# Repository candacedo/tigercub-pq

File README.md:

# TigerCub PocketQube Platform
TigerCub, an accessible, mission-agnostic PocketQube platform.

TigerCub is a satellite bus in the PocketQube form factor, designed to be accessible to students and amateur nanosatellite developers. It uses primarily commercial-off-the-shelf (COTS) components and relatively simple custom-designed PCBs, lowering barriers of entry for developers who are venturing into the PocketQube world. 

I developed TigerCub for my undergraduate senior independent work. The vast majority of design work is complete and some subsystems have been tested in laboratory environments, but the satellite bus has yet to undergo full functional testing and testing in flight-like environments. Please use at your own risk.     

## Technical Overview
TigerCub includes the following subsystems:
* on-board computer and attitude determination system,
* electrical power system,
* radio communication system, and 
* chassis.

The on-board computer/attitude determination system features an Arduino-programmable Teensy 4.0 as well as a COTS IMU and COTS MicroSD storage from SparkFun. The communication system uses the RockBLOCK 9603, a compact and lightweight communications module that transmits and receives via the Iridium network. The electrical power system is composed of a power management and distribution module designed by BHDynamics, custom-designed solar panels, and a Lithium-ion battery. These subsystems are all integrated into a sheet-metal chassis, with additional space for a payload. 

All CAD was created in PTC Creo Parametric (Version 9.0.0.0), which is free for students. All schematics and PCB designs were created in KiCAD, a free EDA software. 

## Documentation
For additional technical and operational details, including design decisions, bill of materials, power and thermal analyses, and sample code, see the "TigerCub_Report" PDF file in the repository. Please reach out to cdo32 \[at\] gatech \[dot\] edu or mgalvin \[at\] princeton \[dot\] edu for further questions. 

## Future Work & Things to Fix
A few features that should to be fixed/added (not an exhaustive list):
* Kill switches should serve as a break point between the battery and the on-board computer instead of just being connected to the on-board computer. This will involve some redesign of the backplate and wire routing. 
* Flight software needs to be developed for the EPS module and expanded upon for the flight computer. (See technical report for additional details.)
* The RockBLOCK radio system has two electrolyic supercapacitors that are a potential outgassing risk. These should be swapped out for space-qualified capacitors.
* The thermal analysis (see technical report) suggests that the spacecraft may operate outside the temperature limits of the battery. The battery should be insulated to protect it from temperature extremes. See technical report for a few suggestions.

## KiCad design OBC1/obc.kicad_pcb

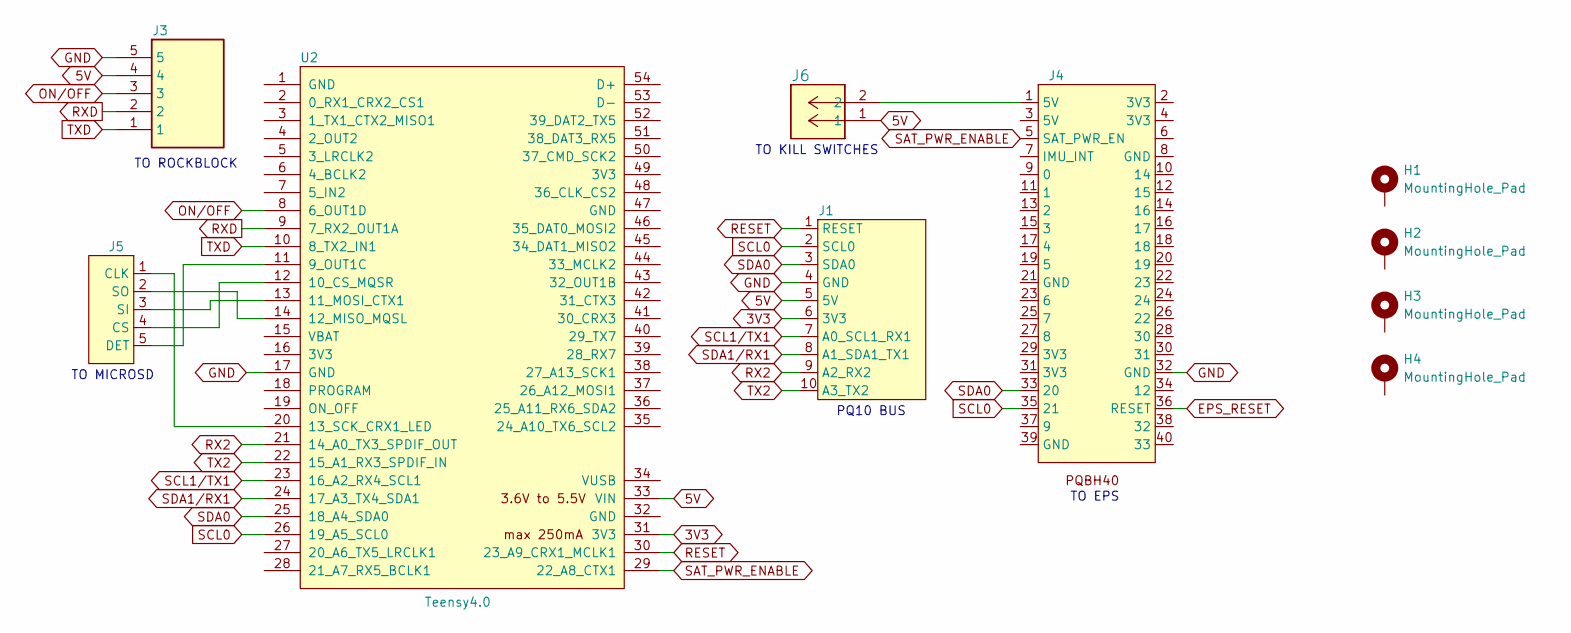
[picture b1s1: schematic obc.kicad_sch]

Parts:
H1, H2, H3, H4: MountingHole_Pad; MountingHole_2.5mm_Pad
J1: PinSocket_1x10_P2.00mm_Vertical
J2: (no value)
J3: 53048-0510; 530480510; Mouser Part Number 538-53048-0510
J4: PinSocket_2x20_P1.27mm_Vertical
J5: PinSocket_1x05_P2.00mm_Vertical
J6: 530480210; Molex_Picoblade_2x1_horz
U2: Teensy4.0; Teensy40

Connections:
3V3: J1.6 (3V3), U2.31 (3V3)
5V: J1.5 (5V), J3.4, J6.1, U2.33 (VIN)
EPS_RESET: J4.36 (RESET)
GND: J1.4 (GND), J3.5, J4.32 (GND), U2.17 (GND)
unnamed: J4.1 (5V), J6.2
unnamed: J5.1 (CLK), U2.20 (13_SCK_CRX1_LED)
unnamed: J5.4 (CS), U2.12 (10_CS_MQSR)
unnamed: J5.5 (DET), U2.11 (9_OUT1C)
unnamed: J5.3 (SI), U2.13 (11_MOSI_CTX1)
unnamed: J5.2 (SO), U2.14 (12_MISO_MQSL)
ON/OFF: J3.3, U2.8 (6_OUT1D)
RESET: J1.1 (RESET), U2.30 (23_A9_CRX1_MCLK1)
RX2: J1.9 (A2_RX2), U2.21 (14_A0_TX3_SPDIF_OUT)
RXD: J3.2, U2.9 (7_RX2_OUT1A)
SAT_PWR_ENABLE: J4.5 (SAT_PWR_EN), U2.29 (22_A8_CTX1)
SCL0: J1.2 (SCL0), J4.35 (21), U2.26 (19_A5_SCL0)
SCL1/TX1: J1.7 (A0_SCL1_RX1), U2.23 (16_A2_RX4_SCL1)
SDA0: J1.3 (SDA1), J4.33 (20), U2.25 (18_A4_SDA0)
SDA1/RX1: J1.8 (A1_SDA1_TX1), U2.24 (17_A3_TX4_SDA1)
TX2: J1.10 (A3_TX2), U2.22 (15_A1_RX3_SPDIF_IN)
TXD: J3.1, U2.10 (8_TX2_IN1)

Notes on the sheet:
TO KILL SWITCHES
PQ10 BUS
TO ROCKBLOCK
TO EPS
TO MICROSD

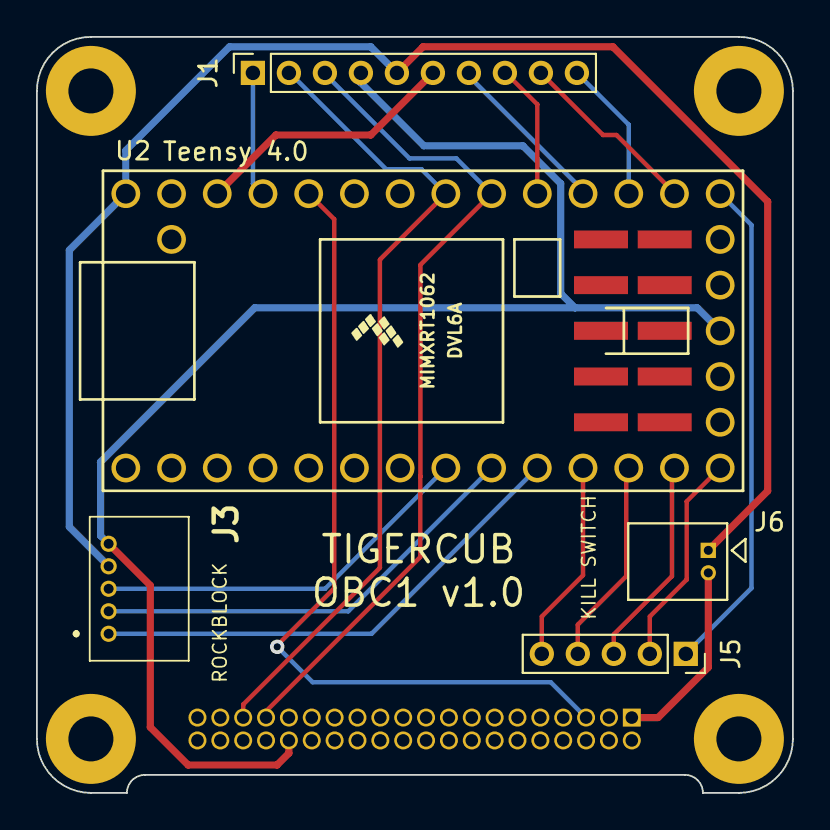
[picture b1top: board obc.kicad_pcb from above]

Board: 2 copper layers, 42.0 x 42.0 mm, 10 parts (1 on the bottom side), 20 nets.

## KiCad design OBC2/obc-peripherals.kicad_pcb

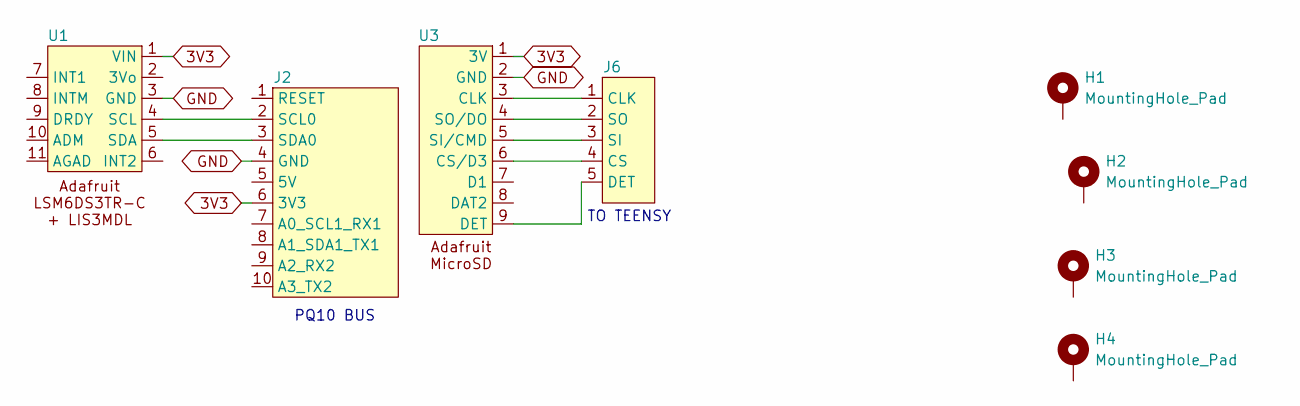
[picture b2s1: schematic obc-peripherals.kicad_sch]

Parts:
H1, H2, H3, H4: MountingHole_Pad; MountingHole_2.5mm_Pad
J2: PinSocket_1x10_P2.00mm_Vertical
J6: PinSocket_1x05_P2.00mm_Vertical
U1: Adafruit_LSM6DS3TR-C_LIS3MDL
U3: Adafruit_MicroSD

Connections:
unnamed: J2.6 (3V3), U1.1 (VIN), U3.1 (3V)
unnamed: J2.4 (GND), U1.3 (GND), U3.2 (GND)
unnamed: J2.2 (SCL0), U1.4 (SCL)
unnamed: J2.3 (SDA1), U1.5 (SDA)
unnamed: J6.1 (CLK), U3.3 (CLK)
unnamed: J6.4 (CS), U3.6 (CS/D3)
unnamed: J6.5 (DET), U3.9 (DET)
unnamed: J6.3 (SI), U3.5 (SI/CMD)
unnamed: J6.2 (SO), U3.4 (SO/DO)

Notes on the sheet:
PQ10 BUS
TO TEENSY

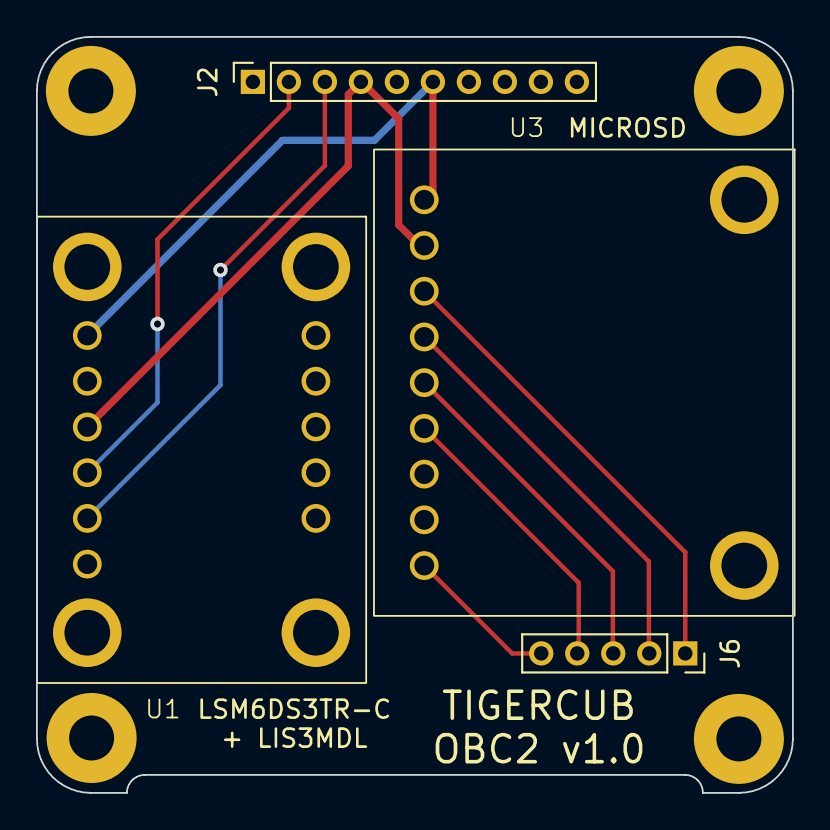
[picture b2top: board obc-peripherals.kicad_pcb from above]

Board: 2 copper layers, 42.0 x 42.0 mm, 8 parts (0 on the bottom side), 9 nets.

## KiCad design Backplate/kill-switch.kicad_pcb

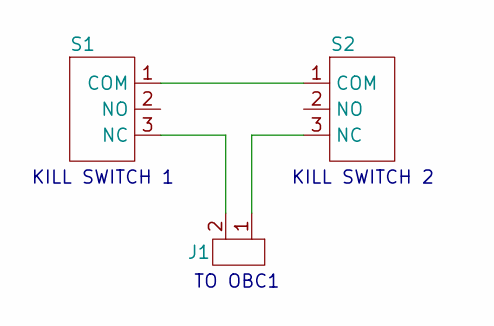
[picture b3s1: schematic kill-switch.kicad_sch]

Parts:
J1: Molex_Picoblade_2x1_vert
S1: D2F-L2-A
S2: D2F-L2-A1

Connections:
unnamed: S1.1 (COM), S2.1 (COM)
unnamed: J1.2, S1.3 (NC)
unnamed: J1.1, S2.3 (NC)

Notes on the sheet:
KILL SWITCH 1
TO OBC1
KILL SWITCH 2

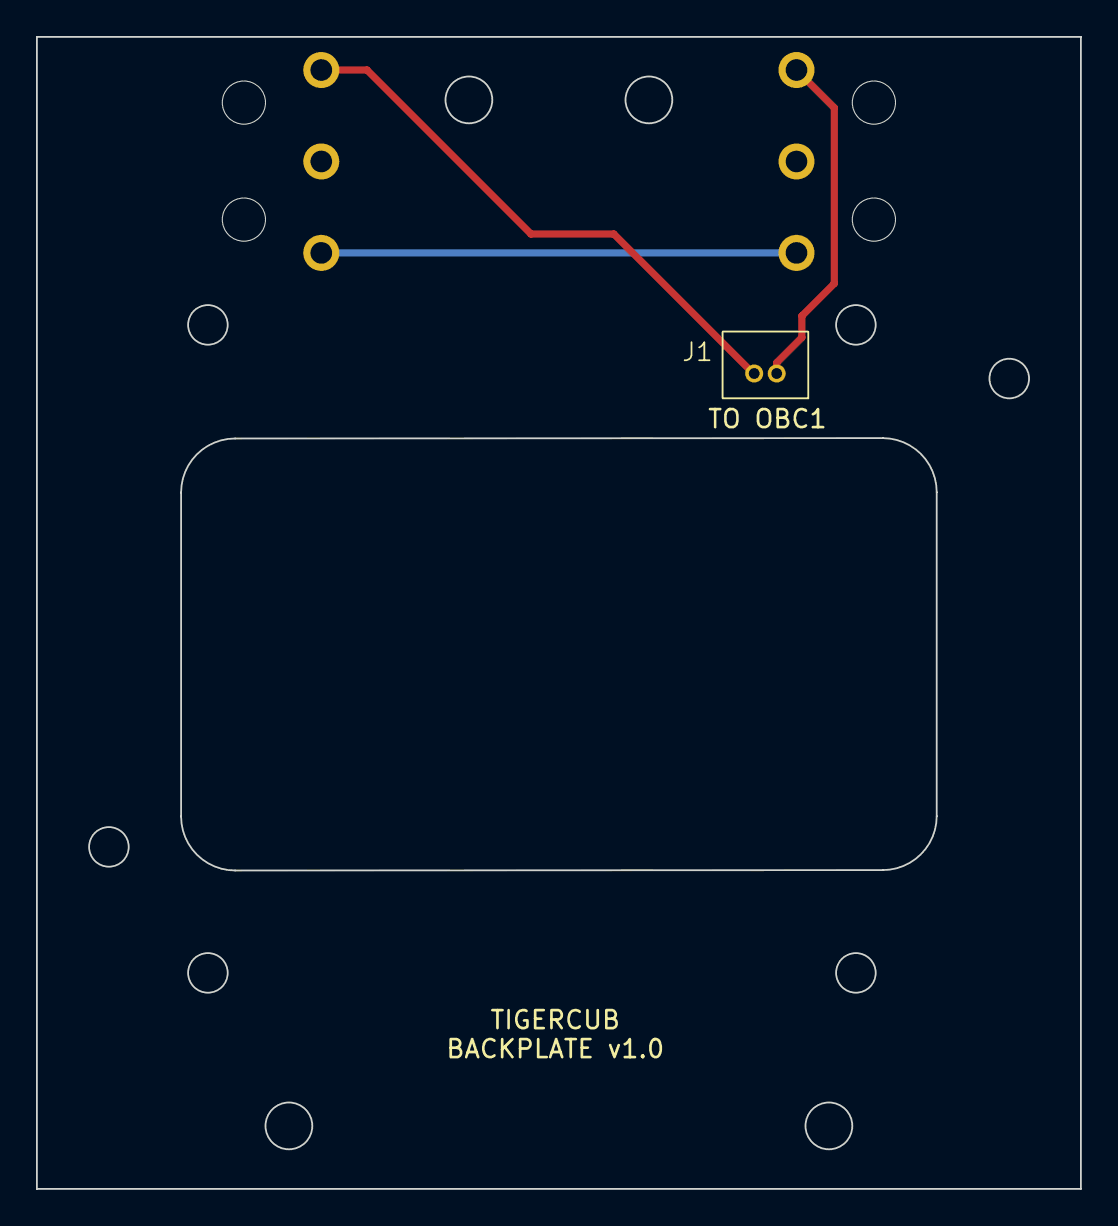
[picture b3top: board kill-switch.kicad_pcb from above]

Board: 2 copper layers, 58.0 x 64.0 mm, 3 parts (0 on the bottom side), 3 nets.

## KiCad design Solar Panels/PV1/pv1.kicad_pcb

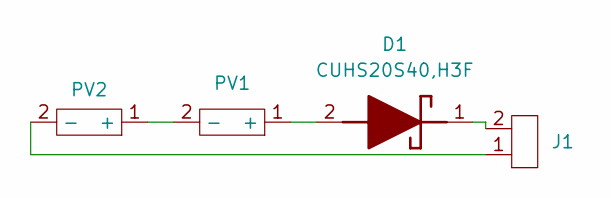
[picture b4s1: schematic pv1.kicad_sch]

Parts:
D1: CUHS20S40,H3F; CUHS20S40H3F; Mouser Part Number 757-CUHS20S40H3F
J1: Molex_PicoBlade_53048-0210_1x02_P1.25mm_Horizontal
PV1, PV2: SM940K09L

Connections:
unnamed: D1.2 (A), PV1.1 (+)
unnamed: D1.1 (K), J1.2
unnamed: PV1.2 (-), PV2.1 (+)
unnamed: J1.1, PV2.2 (-)

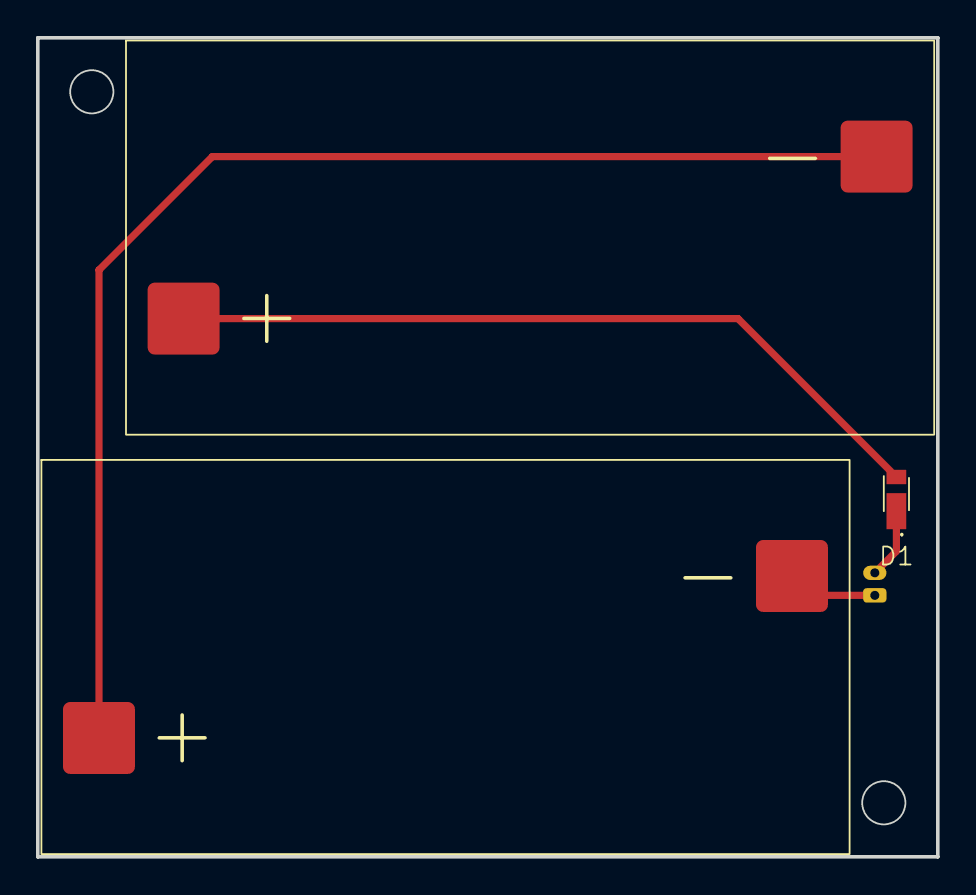
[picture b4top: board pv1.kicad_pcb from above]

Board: 2 copper layers, 50.0 x 45.5 mm, 4 parts (1 on the bottom side), 4 nets.

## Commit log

2024-08-21 readme update
2025-03-16 initial upload of project files
2025-03-24 adding final report
2025-03-25 updating report
